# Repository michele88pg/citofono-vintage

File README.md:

# Pronto â€” a smart door intercom inside a vintage rotary phone

ðŸ‡¬ðŸ‡§ English Â· [ðŸ‡®ðŸ‡¹ Italiano](#-versione-italiana)

**Pronto** is an open-hardware circuit board that turns a vintage rotary phone into a **smart door intercom**. The phone looks and works exactly as before:

- lift the handset to talk to whoever rang;
- dial a number and the street door opens.

On top of that you get:

- a notification on your phone when someone rings;
- remote door opening;
- Home Assistant integration and, through Home Assistant, Google Home, Apple Home and Alexa.

The board has **exactly the shape of the original one** and screws into its place, with no drilling or changes to the shell.

> **Compatibility:** **Siemens / Italtel S62** phones (wall-mounted version) and **URMET 4+N** analog intercom systems, very common in Italian apartment buildings.
> Other phones and systems: see [Compatibility](docs/compatibilita.md) (in Italian).

---

> [!WARNING]
> **Prototype stage.** Board rev 0.5 has been ordered (5 assembled boards) but **has not been tested yet**.
> The firmware is validated, but not yet tried on real hardware.
> You are welcome to build one now, but expect to fix something along the way. Current status is in the [CHANGELOG](CHANGELOG.md).

## Contents

- [What it does](#what-it-does)
- [How it works, in short](#how-it-works-in-short)
- [Board pinout](#board-pinout)
- [What you need](#what-you-need)
- [Getting started](#getting-started)
- [Repository layout](#repository-layout)
- [Roadmap](#roadmap)
- [Safety](#safety)
- [Contributing](#contributing)
- [Licenses](#licenses)
- [ðŸ‡®ðŸ‡¹ Versione italiana](#-versione-italiana)

## What it does

| Feature | How it works |
|---|---|
| **Answering** | As always: lift the handset and talk. Audio passes through in analog form; the board does not touch it |
| **Open with the dial** | Dial any number and the door opens, as many vintage intercom phones did. Optional: a **secret code** to dial |
| **Ringing** | When someone rings at the street door, the board's buzzer plays a classic double ring. The phone's original bells can be connected experimentally |
| **Phone notification** | A notification arrives with an **"Open the door"** button in it |
| **Remote opening** | From Home Assistant, the notification, a voice assistant or the board's own web page |
| **Do not disturb** | Silences the ring; the notification still arrives |
| **Auto-open** | Opens by itself when someone rings, handy for parties or expected deliveries. Turns itself off on reboot |
| **History** | Last call, last opening, call counter |
| **Local web page** | `http://citofono-vintage.local` works even without Home Assistant |
| **Remote listening and talking** | *In development:* an add-on audio board with an ES8311 codec. See [hardware/audio-board](hardware/audio-board/README.md) |

## How it works, in short

```mermaid
flowchart LR
    subgraph IMP["URMET 4+N intercom system"]
        CA["CA: call"]
        APR["9 and 6: door release"]
        FON["1 and 2: audio"]
    end
    subgraph SCH["Pronto board, inside the phone"]
        OK1["OK1 optocoupler<br/>detects the call"]
        K1["K1 PhotoMOS<br/>opens the door"]
        K2["K2 PhotoMOS<br/>simulates handset lifted"]
        ESP["ESP32-S3<br/>ESPHome firmware"]
        BZ["Buzzer"]
    end
    subgraph TEL["Rotary phone"]
        DISCO["Rotary dial"]
        CORN["Handset and hook switch"]
    end
    HA["Home Assistant<br/>notifications, Google, Apple, Alexa"]
    CA --> OK1 --> ESP
    ESP --> K1 --> APR
    ESP --> K2 -->|enables| FON
    DISCO --> ESP
    CORN --> ESP
    FON <-->|analog audio| CORN
    ESP --> BZ
    ESP <-->|WiFi| HA
```

**Isolation from the building system.** The board has no direct electrical connection to the shared intercom line. It detects the call with an optocoupler and opens the door with PhotoMOS solid-state relays, which are optically isolated. The electronics' ground stays separate from the intercom line.

The full description is in **[docs/come-funziona.md](docs/come-funziona.md)** (in Italian): every circuit block, the opening sequences, dial timing and firmware safety features.

## Board pinout

The labels are in Italian. Key terms:

| Label | Meaning |
|---|---|
| alimentazione | power input |
| cornetta, capsula, microfono | handset, earpiece, microphone |
| gancio | hook switch |
| fonia entrata / uscita | audio in (from street) / audio out (to street) |
| comune | common |
| apriporta | door release |
| chiamata | call |
| suoneria | ringer bells |
| disco, impulsi, rotazione | dial, pulses, dial-in-motion contact |
| massa | ground |
| zona linea / zona logica | intercom-line side / isolated logic side |
| barriera di isolamento | isolation barrier |

Step-by-step wiring of dial, hook, handset and intercom is in [docs/installazione.md](docs/installazione.md).

## What you need

| Item | Notes |
|---|---|
| An **S62 wall phone** | Found at flea markets and online. Dial, handset and hook switch must work |
| The **Pronto** board | Order it pre-assembled from JLCPCB with the ready-made files in [`hardware/mainboard/production`](hardware/mainboard/production): see [Ordering the board](docs/ordinare-la-scheda.md) |
| Hand-soldered parts | The K1 relay (through-hole, from DigiKey/Mouser) and the screw terminals. Easy soldering |
| **Power** | URMET 4+N systems do not power the indoor unit. You need a supply on J1, **9â€“36 V DC or 9â€“24 V AC** (for example 12 V DC, 1 A), or **5 V from USB-C** |
| Home WiFi | Home Assistant is recommended but not required |
| Tools | Soldering iron, multimeter, screwdriver. A computer with [ESPHome](https://esphome.io) for the first firmware upload over USB-C |

Indicative parts cost is about â‚¬40 per board for 5 assembled prototypes. It drops a lot with larger quantities.

## Getting started

The detailed guides are currently in Italian; translations are welcome.

1. **Check compatibility** of your intercom and phone: [docs/compatibilita.md](docs/compatibilita.md)
2. **Order and assemble the board:** [docs/ordinare-la-scheda.md](docs/ordinare-la-scheda.md)
3. **Upload the firmware:** [firmware/README.md](firmware/README.md)
4. **Install the board in the phone and wire it to the intercom:** [docs/installazione.md](docs/installazione.md)
5. **Test it, one step at a time:** [docs/collaudo.md](docs/collaudo.md)
6. **Connect Home Assistant and notifications:** [docs/home-assistant.md](docs/home-assistant.md)

FAQ: [docs/faq.md](docs/faq.md)

## Repository layout

```
citofono-vintage/
â”œâ”€â”€ hardware/
â”‚   â”œâ”€â”€ mainboard/          Main board (KiCad): schematic, PCB, PDF
â”‚   â”‚   â””â”€â”€ production/     Gerber, BOM and placement files ready for JLCPCB
â”‚   â”œâ”€â”€ audio-board/        ES8311 audio board (remote listen/talk), schematic only
â”‚   â””â”€â”€ mechanical/         S62 board outline as DXF
â”œâ”€â”€ firmware/               ESPHome firmware (+ package for the audio board)
â”œâ”€â”€ home-assistant/         Example automations (notification with "Open" button)
â”œâ”€â”€ docs/                   Documentation: how it works, installation, testing...
â”œâ”€â”€ LICENSES/               License texts
â””â”€â”€ CHANGELOG.md            Revision history
```

## Roadmap

- [x] Mechanical survey of the original S62 board and DXF outline
- [x] Schematic and PCB rev 0.5 in the original board's shape
- [x] ESPHome firmware with dial opening, notifications and remote opening
- [x] Audio board schematic (ES8311) for remote listening and talking
- [ ] Testing the rev 0.5 prototypes on a real URMET system
- [ ] Audio board PCB and voice calls on the phone
- [ ] Photo assembly guide and project website
- [ ] Cheaper, simplified board (ESP32 chip directly on the board, fewer parts)
- [ ] Support for other 4+N systems and other rotary phones
- [ ] English translation of the documentation

## Safety

- The board works only with **extra-low voltages**: 12 V AC call signal, at most about 30 V DC on the intercom line, 9â€“36 V supply. **Never connect it to 230 V mains.**
- The intercom system is often **shared by the whole building**. Make sure you are allowed to work on your indoor unit. Disconnect the old intercom only after identifying the terminals with a multimeter.
- Remote opening really opens your front door. Protect Home Assistant and the board's web page with strong passwords, and never expose the board directly to the Internet.
- The project is provided **as is**, without warranty (see [Licenses](#licenses)). Whoever builds and installs it is responsible for it.

## Contributing

The most valuable contribution right now is knowing **which intercom systems and phones it works with**.
If you try it, open a [compatibility report](../../issues/new?template=compatibilita.md), even if it does not work. Include make and model of the intercom and phone, and your measurements.

Fixes, assembly photos and translations are welcome: see [CONTRIBUTING.md](CONTRIBUTING.md).

## Licenses

| Part | License |
|---|---|
| Hardware (`hardware/`) | [CERN-OHL-S v2](LICENSES/CERN-OHL-S-2.0.txt) |
| Firmware and configuration (`firmware/`, `home-assistant/`) | [MIT](LICENSES/MIT.txt) |
| Documentation and images (`docs/`, `.md` files) | [CC BY-SA 4.0](LICENSES/CC-BY-SA-4.0.txt) |

Details are in [LICENSE.md](LICENSE.md).

**Trademarks.** Siemens, Italtel and URMET are trademarks of their respective owners. They are mentioned only to indicate compatibility. This is an independent project, not affiliated with or endorsed by them.
The S62 phone is a classic of Italian industrial design, designed by Lino Saltini in the 1960s. This project does not reproduce its shell: it only replaces the electronics inside.

---

## ðŸ‡®ðŸ‡¹ Versione italiana

[ðŸ‡¬ðŸ‡§ English](#contents) Â· ðŸ‡®ðŸ‡¹ Italiano

**Pronto â€” il citofono smart dentro un telefono a disco**

**Pronto** Ã¨ una scheda elettronica open hardware che trasforma un telefono a disco d'epoca in un **citofono smart**. Il telefono resta com'Ã¨, fuori e nell'uso:

- alzi la cornetta per parlare con chi ha suonato;
- componi un numero con il disco e il portone si apre.

In piÃ¹ arrivano:

- la notifica sul cellulare quando qualcuno suona;
- l'apertura del portone da remoto;
- l'integrazione con Home Assistant e, tramite Home Assistant, con Google Home, Apple Home e Alexa.

La scheda ha **esattamente la forma della scheda originale** e si avvita al suo posto, senza forare nÃ© modificare il guscio.

> **CompatibilitÃ :** telefoni **Siemens / Italtel S62** (versione da parete) e impianti citofonici **URMET 4+N** analogici.
> Altri telefoni e impianti: vedi [CompatibilitÃ ](docs/compatibilita.md).

> [!WARNING]
> **Progetto in fase di prototipo.** La scheda rev 0.5 Ã¨ stata ordinata (5 esemplari assemblati) ma **non Ã¨ ancora stata collaudata**.
> Il firmware Ã¨ validato, ma non ancora provato sull'hardware vero.
> Se vuoi costruirla adesso sei il benvenuto, ma aspettati di dover correggere qualcosa. Lo stato aggiornato Ã¨ nel [CHANGELOG](CHANGELOG.md).

### Indice

- [Cosa fa](#cosa-fa)
- [Come funziona in breve](#come-funziona-in-breve)
- [Mappa dei morsetti](#mappa-dei-morsetti)
- [Cosa serve](#cosa-serve)
- [Da dove iniziare](#da-dove-iniziare)
- [Struttura della repository](#struttura-della-repository)
- [Prossimi passi](#prossimi-passi)
- [Sicurezza](#sicurezza)
- [Contribuire](#contribuire)
- [Licenze](#licenze)

### Cosa fa

| Funzione | Come si usa |
|---|---|
| **Rispondere** | Come sempre: alzi la cornetta e parli. L'audio passa in analogico, la scheda non lo tocca |
| **Aprire con il disco** | Componi un numero qualsiasi e il portone si apre, come facevano molti citofoni-telefono d'epoca. Opzionale: un **codice segreto** da comporre |
| **Suoneria** | Quando suonano al portone, il buzzer della scheda squilla con un doppio squillo da telefono. La suoneria originale a campanelli si puÃ² collegare in via sperimentale |
| **Notifica sul cellulare** | Arriva una notifica con il pulsante **"Apri il portone"** dentro |
| **Apertura remota** | Da Home Assistant, dalla notifica, dall'assistente vocale o dalla pagina web della scheda |
| **Non disturbare** | Silenzia lo squillo; la notifica arriva comunque |
| **Apertura automatica** | Apre da sola alla chiamata, utile per feste o consegne attese. Si disattiva da sola al riavvio |
| **Storico** | Ultima chiamata, ultima apertura, contatore delle chiamate |
| **Pagina web locale** | `http://citofono-vintage.local` funziona anche senza Home Assistant |
| **Ascolto e risposta da remoto** | *In sviluppo:* scheda audio aggiuntiva con codec ES8311. Vedi [hardware/audio-board](hardware/audio-board/README.md) |

### Come funziona in breve

```mermaid
flowchart LR
    subgraph IMP["Impianto citofonico URMET 4+N"]
        CA["CA: chiamata"]
        APR["9 e 6: apriporta"]
        FON["1 e 2: fonia"]
    end
    subgraph SCH["Scheda Pronto, dentro il telefono"]
        OK1["OK1 optoisolatore<br/>sente la chiamata"]
        K1["K1 PhotoMOS<br/>apre il portone"]
        K2["K2 PhotoMOS<br/>simula la cornetta alzata"]
        ESP["ESP32-S3<br/>firmware ESPHome"]
        BZ["Buzzer"]
    end
    subgraph TEL["Telefono a disco"]
        DISCO["Disco combinatore"]
        CORN["Cornetta e gancio"]
    end
    HA["Home Assistant<br/>notifiche, Google, Apple, Alexa"]
    CA --> OK1 --> ESP
    ESP --> K1 --> APR
    ESP --> K2 -->|abilita| FON
    DISCO --> ESP
    CORN --> ESP
    FON <-->|audio analogico| CORN
    ESP --> BZ
    ESP <-->|WiFi| HA
```

**Isolamento dall'impianto.** La scheda non ha nessun collegamento elettrico diretto con l'impianto condominiale. Sente la chiamata con un optoisolatore e apre il portone con relÃ¨ allo stato solido PhotoMOS, che isolano otticamente. La massa dell'elettronica resta cosÃ¬ separata dalla linea del citofono.

Il funzionamento completo Ã¨ in **[docs/come-funziona.md](docs/come-funziona.md)**: ogni blocco del circuito, le sequenze di apertura, i tempi del disco e le sicurezze del firmware.

### Mappa dei morsetti

Il collegamento passo passo di disco, gancio, cornetta e citofono Ã¨ in [docs/installazione.md](docs/installazione.md).

### Cosa serve

| Cosa | Note |
|---|---|
| Un telefono **S62 da parete** | Si trova nei mercatini e online. Deve avere disco, cornetta e gancio funzionanti |
| La scheda **Pronto** | Si ordina giÃ  assemblata da JLCPCB con i file pronti in [`hardware/mainboard/production`](hardware/mainboard/production): vedi [Ordinare la scheda](docs/ordinare-la-scheda.md) |
| Componenti da saldare a mano | Il relÃ¨ K1 (a foro passante, da DigiKey/Mouser) e le morsettiere a vite. Sono saldature facili |
| **Alimentazione** | L'impianto URMET 4+N non alimenta il posto interno. Serve un alimentatore su J1, **9â€“36 V DC o 9â€“24 V AC** (per esempio 12 V DC da 1 A), oppure **5 V da USB-C** |
| WiFi di casa | Home Assistant Ã¨ consigliato ma non obbligatorio |
| Attrezzatura | Saldatore, tester, cacciavite. Un computer con [ESPHome](https://esphome.io) per il primo caricamento del firmware via USB-C |

Il costo indicativo dei componenti Ã¨ di circa 40 â‚¬ a scheda su 5 prototipi assemblati. Scende molto con quantitÃ  maggiori.

### Da dove iniziare

1. **Verifica la compatibilitÃ ** del tuo impianto e del tuo telefono: [docs/compatibilita.md](docs/compatibilita.md)
2. **Ordina e monta la scheda:** [docs/ordinare-la-scheda.md](docs/ordinare-la-scheda.md)
3. **Carica il firmware:** [firmware/README.md](firmware/README.md)
4. **Installa la scheda nel telefono e collegala al citofono:** [docs/installazione.md](docs/installazione.md)
5. **Collauda, un passo alla volta:** [docs/collaudo.md](docs/collaudo.md)
6. **Collega Home Assistant e le notifiche:** [docs/home-assistant.md](docs/home-assistant.md)

Domande frequenti: [docs/faq.md](docs/faq.md)

### Struttura della repository

```
citofono-vintage/
â”œâ”€â”€ hardware/
â”‚   â”œâ”€â”€ mainboard/          Scheda principale (KiCad): schema, PCB, PDF
â”‚   â”‚   â””â”€â”€ production/     Gerber, BOM e posizionamento pronti per JLCPCB
â”‚   â”œâ”€â”€ audio-board/        Scheda audio ES8311 (ascolto e risposta da remoto), solo schema
â”‚   â””â”€â”€ mechanical/         Contorno della scheda S62 in DXF
â”œâ”€â”€ firmware/               Firmware ESPHome (+ pacchetto per la scheda audio)
â”œâ”€â”€ home-assistant/         Automazioni di esempio (notifica con pulsante "Apri")
â”œâ”€â”€ docs/                   Documentazione: funzionamento, installazione, collaudo...
â”œâ”€â”€ LICENSES/               Testi delle licenze
â””â”€â”€ CHANGELOG.md            Storia delle revisioni
```

### Prossimi passi

- [x] Rilievo meccanico della scheda originale S62 e contorno in DXF
- [x] Schema elettrico e PCB rev 0.5 nella forma della scheda originale
- [x] Firmware ESPHome con apertura da disco, notifiche e apertura remota
- [x] Schema della scheda audio (ES8311) per ascolto e risposta da remoto
- [ ] Collaudo dei prototipi rev 0.5 su impianto URMET reale
- [ ] PCB della scheda audio e integrazione della chiamata vocale sul cellulare
- [ ] Guida fotografica al montaggio e sito del progetto
- [ ] Versione piÃ¹ economica e semplificata della scheda (ESP32 direttamente sulla scheda, meno componenti)
- [ ] CompatibilitÃ  con altri impianti 4+N e con altri telefoni a disco
- [ ] Traduzione in inglese della documentazione

### Sicurezza

- La scheda lavora solo con **bassissime tensioni**: 12 V AC di chiamata, al massimo circa 30 V DC sulla linea citofonica, 9â€“36 V di alimentazione. **Non va mai collegata alla rete a 230 V.**
- L'impianto citofonico Ã¨ spesso **condominiale**. Prima di intervenire sul tuo posto interno, verifica di poterlo fare. Scollega il vecchio citofono solo dopo aver identificato i morsetti con il tester.
- L'apertura remota apre davvero il portone di casa. Proteggi Home Assistant e la pagina web della scheda con password robuste, e non esporre la scheda direttamente su Internet.
- Il progetto Ã¨ fornito **cosÃ¬ com'Ã¨**, senza garanzie (vedi [Licenze](#licenze)). Chi lo costruisce e lo installa ne Ã¨ responsabile.

### Contribuire

Il contributo piÃ¹ prezioso adesso Ã¨ sapere **su quali impianti e telefoni funziona**.
Se lo provi, apri una [segnalazione di compatibilitÃ ](../../issues/new?template=compatibilita.md), anche se non funziona. Servono marca e modello dell'impianto e del telefono, e le misure fatte.

Correzioni, foto del montaggio e traduzioni sono benvenute: vedi [CONTRIBUTING.md](CONTRIBUTING.md).

### Licenze

| Parte | Licenza |
|---|---|
| Hardware (`hardware/`) | [CERN-OHL-S v2](LICENSES/CERN-OHL-S-2.0.txt) |
| Firmware e configurazioni (`firmware/`, `home-assistant/`) | [MIT](LICENSES/MIT.txt) |
| Documentazione e immagini (`docs/`, file `.md`) | [CC BY-SA 4.0](LICENSES/CC-BY-SA-4.0.txt) |

I dettagli sono in [LICENSE.md](LICENSE.md).

**Marchi.** Siemens, Italtel e URMET sono marchi dei rispettivi proprietari. Sono citati solo per indicare la compatibilitÃ . Questo Ã¨ un progetto indipendente, non affiliato nÃ© approvato da loro.
Il telefono S62 Ã¨ un classico del design industriale italiano, disegnato da Lino Saltini negli anni '60. Questo progetto non ne riproduce il guscio: ne sostituisce solo l'elettronica interna.

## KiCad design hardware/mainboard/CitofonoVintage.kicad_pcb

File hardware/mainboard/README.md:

# Scheda principale (rev 0.5)

## File

| File | Contenuto |
|---|---|
| `CitofonoVintage.kicad_pro` | Progetto KiCad: apri questo. Contiene regole e classi di rete |
| `CitofonoVintage.kicad_sch` | Schema elettrico, con il campo **LCSC Part#** su ogni componente |
| `CitofonoVintage.kicad_pcb` | Circuito stampato sbrogliato |
| `CitofonoVintage_schematic.pdf` | Schema stampabile |
| `board_layers.pdf` | Strati del PCB. Stampato in scala 1:1 serve a verificare l'ingombro nel telefono |
| [`production/`](production) | Gerber, BOM e CPL per l'ordine assemblato su JLCPCB |

Il progetto è stato sviluppato con **KiCad 10**, che apre anche i file dei formati precedenti. Tutti i simboli e i footprint vengono dalle librerie ufficiali di KiCad e sono incorporati nei file, quindi non servono librerie esterne.

## Caratteristiche

| | |
|---|---|
| Dimensioni | 81 × 85 mm, contorno identico alla scheda originale S62 ([DXF](../mechanical/S62_board_outline.dxf)) |
| Strati | 2, FR-4 da 1,6 mm, rame da 1 oz |
| Alimentazione | 9–36 V DC o 9–24 V AC su J1, oppure 5 V da USB-C |
| Microcontrollore | ESP32-S3-WROOM-1-N16R2 (16 MB flash, 2 MB PSRAM) |
| Interfaccia linea | Optoisolatore PC817 (chiamata), PhotoMOS TLP3546A/AQV252G (apriporta), PhotoMOS CPC1017N (sgancio) |
| Isolamento | Barriera di 2,4 mm senza rame fra zona linea e zona logica |

## Regole di progetto

| Classe | Pista | Isolamento | Via | Reti |
|---|---|---|---|---|
| Default | 0,25 mm | 0,15 mm | 0,6 / 0,3 mm | segnali |
| Power | 0,5 mm | 0,15 mm | 0,8 / 0,4 mm | +5V, +3V3, +5V_BUCK, VIN_RAW, GND, U1_SW |

Minimi: pista 0,2 mm, via 0,5/0,2 mm, distanza dal bordo 0,2 mm. Sono tutti entro le capacità standard di JLCPCB.

**Zone:**
- `GND_plane`: sullo strato inferiore, solo nella zona logica. La massa è anche sbrogliata con piste, quindi il piano non è l'unico collegamento.
- `isolamento_1…6`: le strisce della barriera. Sono vietati piste, via e rame; pad e componenti sono ammessi, perché OK1, K1 e K2 stanno a cavallo.
- `antenna_keepout`: nessun rame sotto l'antenna del modulo ESP32.

**Stato DRC:** 0 connessioni mancanti e 0 violazioni elettriche. Restano solo avvisi di serigrafia sovrapposta, cosmetici.

## Componenti principali

| Rif | Componente | LCSC | Note |
|---|---|---|---|
| U1 | LM5164DDA (buck 1 A, fino a 100 V) | C477928 | |
| U2 | AMS1117-3.3 | C6186 | |
| U3 | ESP32-S3-WROOM-1-N16R2 | C2913205 | Richiede l'assemblaggio "Standard" |
| K1 | TLP3546A(F) o AQV252G, DIP-6 a foro passante | — | Da saldare a mano, da DigiKey o Mouser |
| K2 | CPC1017N | C81521 | |
| OK1 | PC817 | C3025068 | |
| D1 | ABS10 (ponte) | C400507 | |
| D2 | SMAJ36A (TVS) | C2760877 | |
| L1 | SRR1260-470M (47 µH) | C1329363 | |
| BZ1 | TMB12A05 (buzzer attivo 5 V) | C96093 | |
| J2 | USB-C HRO TYPE-C-31-M-12 | C165948 | |

La distinta completa è in [`production/BOM_JLCPCB.csv`](production/BOM_JLCPCB.csv). I componenti da saldare a mano sono elencati in [docs/ordinare-la-scheda.md](../../docs/ordinare-la-scheda.md#componenti-da-saldare-a-mano).

## Da sistemare nella prossima revisione

- La serigrafia di J1 dice "9-40 V": il valore corretto è **9–36 V DC / 9–24 V AC**, limitato dal TVS D2.
- Nel cartiglio dello schema: la revisione è ancora "0.3" e il titolo del blocco B dice ancora "N16R8" (il modulo montato è l'N16R2).
- Avvisi di serigrafia sovrapposta da ripulire.
- Da valutare dopo il collaudo: i valori di R14 (sensibilità della chiamata) e di R15/R16 (corrente nei LED dei PhotoMOS).

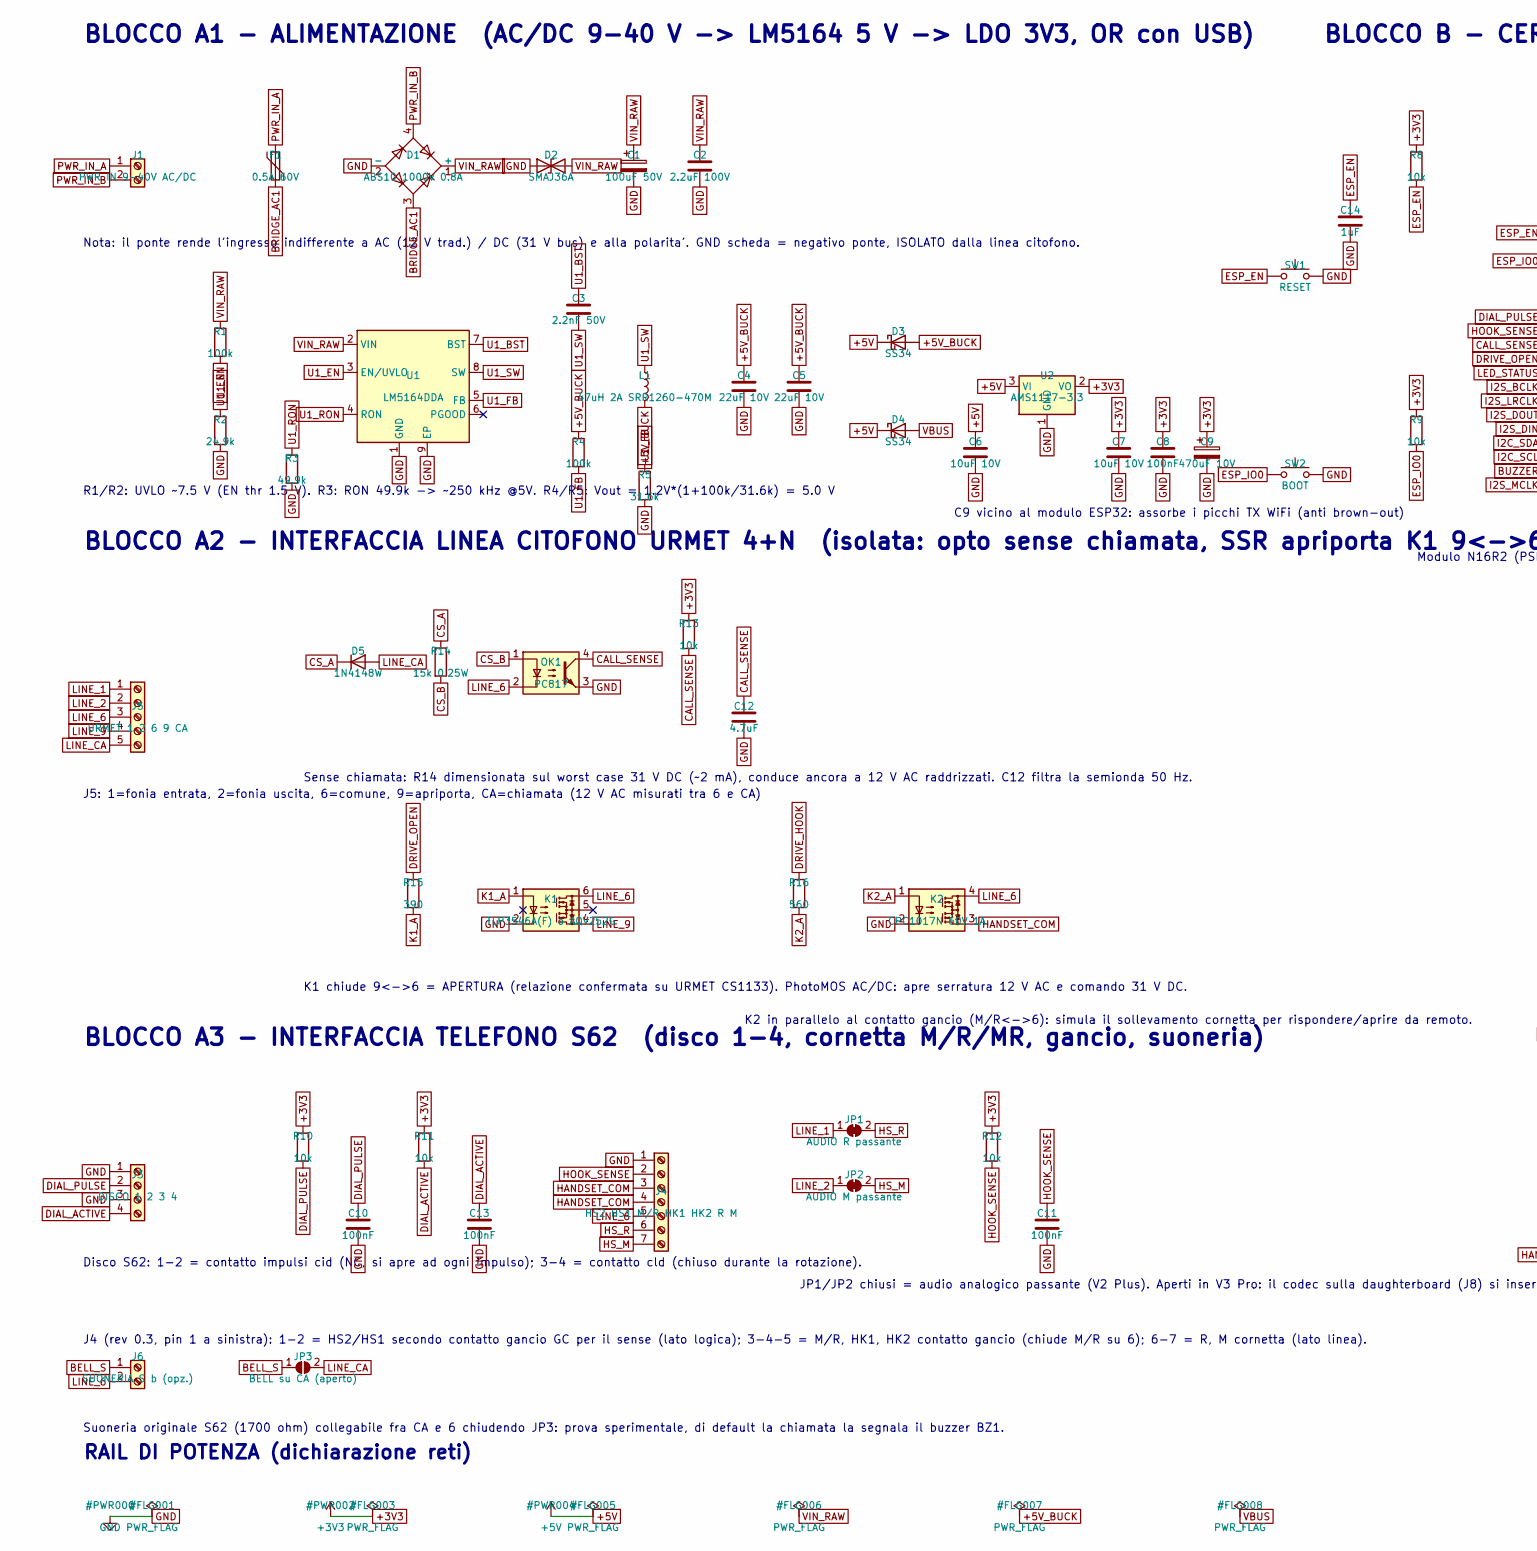
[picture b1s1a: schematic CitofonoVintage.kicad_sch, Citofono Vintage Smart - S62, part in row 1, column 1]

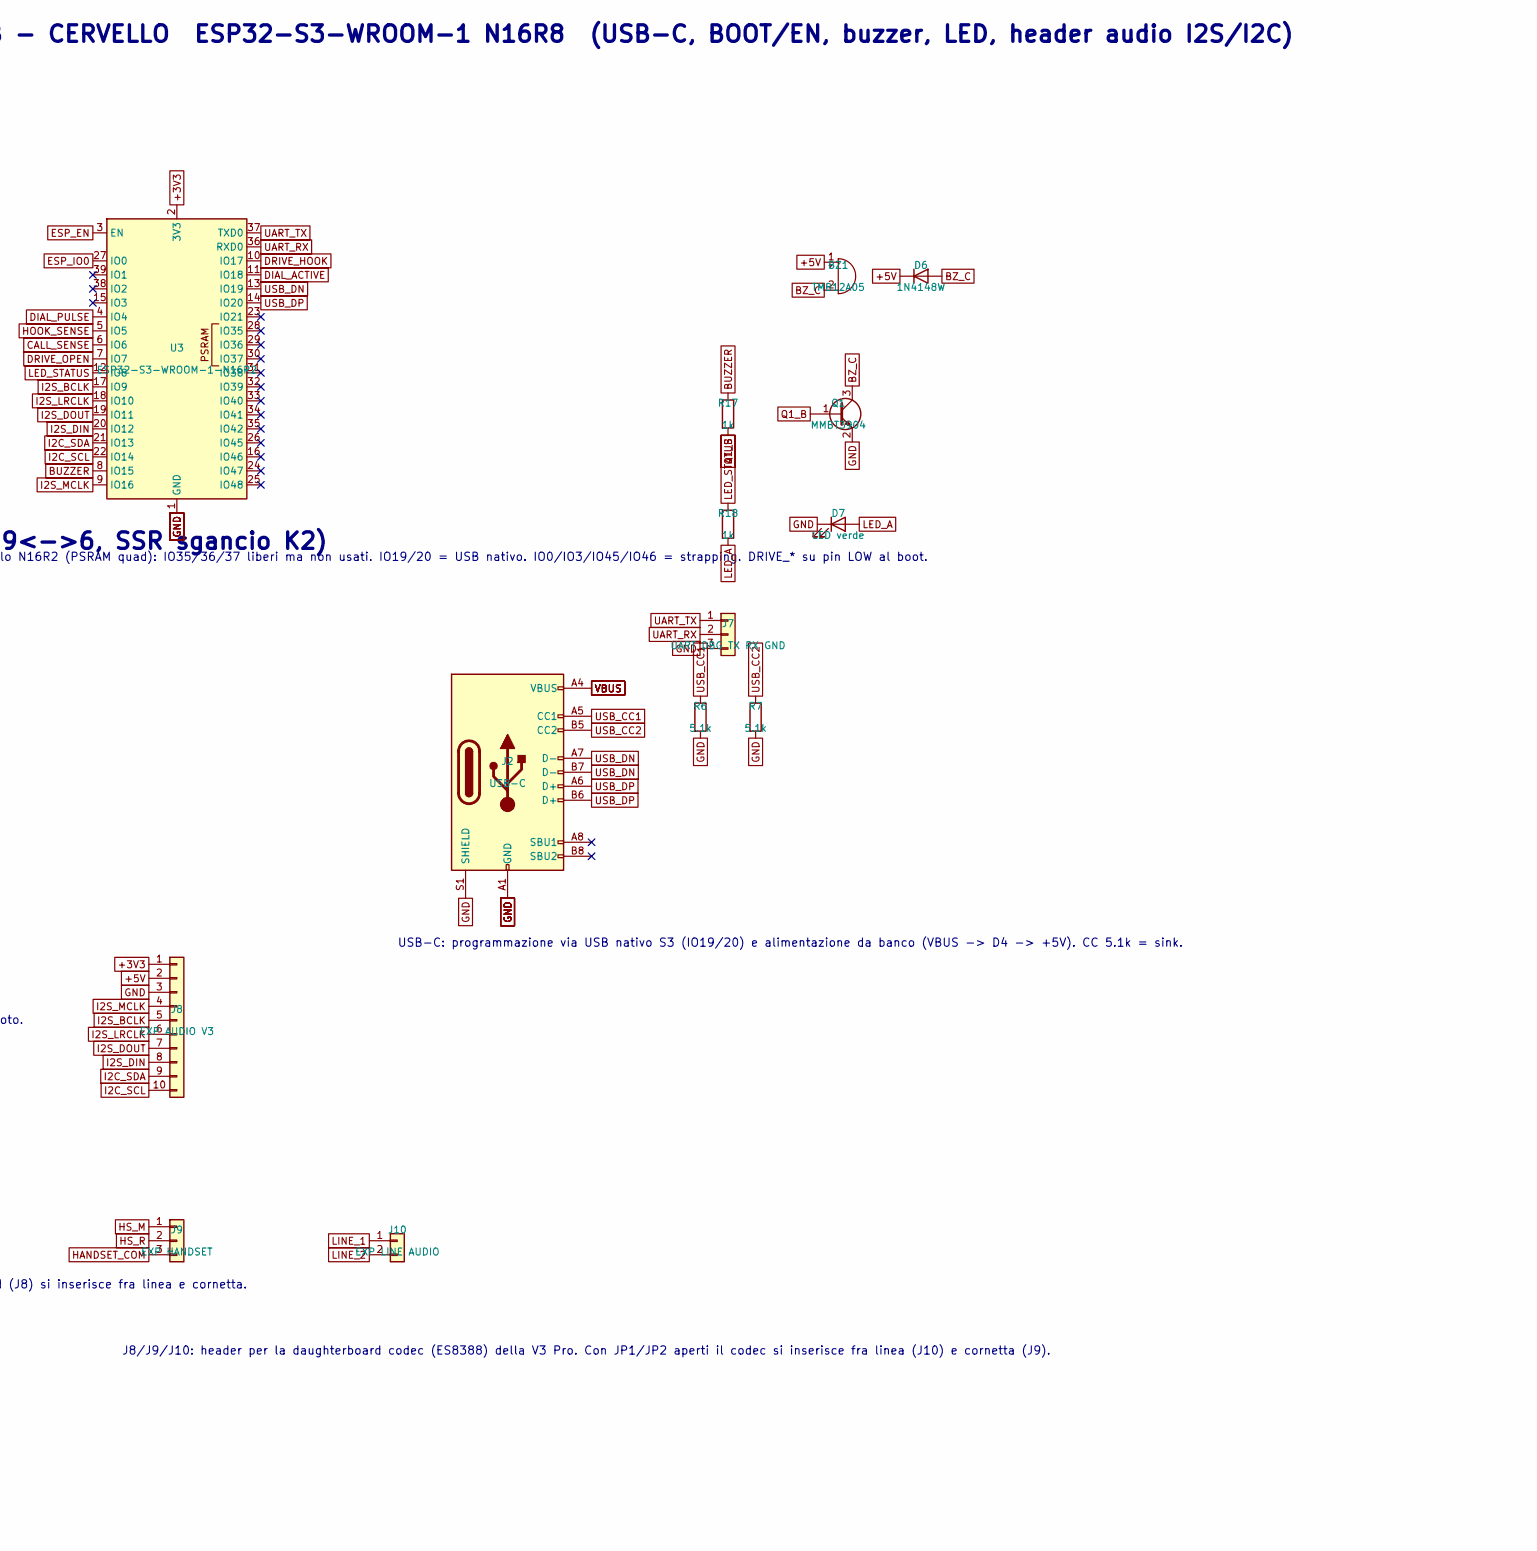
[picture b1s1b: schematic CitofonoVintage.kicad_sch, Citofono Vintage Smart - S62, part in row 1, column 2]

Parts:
BZ1: TMB12A05; Buzzer_12x9.5RM7.6; LCSC Part# C96093
C1: 100uF 50V; CP_Elec_8x10; LCSC Part# C97812
C2: 2.2uF 100V; C_1206_3216Metric; LCSC Part# C577211
C3: 2.2nF 50V; C_0603_1608Metric; LCSC Part# C1604
C4, C5: 22uF 10V; C_0805_2012Metric; LCSC Part# C45783
C6, C7: 10uF 10V; C_0805_2012Metric; LCSC Part# C15850
C8, C10, C11, C13: 100nF; C_0603_1608Metric; LCSC Part# C14663
C9: 470uF 10V; CP_Elec_8x10; LCSC Part# C970706
C12: 4.7uF; C_0805_2012Metric; LCSC Part# C1779
C14: 1uF; C_0603_1608Metric; LCSC Part# C15849
D1: ABS10 1000V 0.8A; Diode_Bridge_Diotec_ABS; LCSC Part# C400507
D2: SMAJ36A; D_SMA; LCSC Part# C2760877
D3, D4: SS34; D_SMA; LCSC Part# C8678
D5, D6: 1N4148W; D_SOD-123; LCSC Part# C81598
D7: LED verde; LED_0805_2012Metric; LCSC Part# C2297
F1: 0.5A 60V; Fuse_1812_4532Metric; LCSC Part# C462518
J1: PWR IN 9-40V AC/DC; TerminalBlock_Phoenix_MKDS-1,5-2_1x02_P5.00mm_Horizontal
J2: USB-C; USB_C_Receptacle_HRO_TYPE-C-31-M-12; LCSC Part# C165948
J3: DISCO 1 2 3 4; TerminalBlock_Phoenix_MKDS-1,5-4_1x04_P5.00mm_Horizontal
J4: HS2 HS1 M/R HK1 HK2 R M; TerminalBlock_Phoenix_MKDS-1,5-7_1x07_P5.00mm_Horizontal
J5: URMET 1 2 6 9 CA; TerminalBlock_Phoenix_MKDS-1,5-5_1x05_P5.00mm_Horizontal
J6: SUONERIA S b (opz.); TerminalBlock_Phoenix_MKDS-1,5-2_1x02_P5.00mm_Horizontal
J7: UART DBG TX RX GND; PinHeader_1x03_P2.54mm_Vertical
J8: EXP AUDIO V3; PinHeader_1x10_P2.54mm_Vertical
J9: EXP HANDSET; PinHeader_1x03_P2.54mm_Vertical
J10: EXP LINE AUDIO; PinHeader_1x02_P2.54mm_Vertical
JP1: AUDIO R passante; SolderJumper-2_P1.3mm_Bridged_RoundedPad1.0x1.5mm
JP2: AUDIO M passante; SolderJumper-2_P1.3mm_Bridged_RoundedPad1.0x1.5mm
JP3: BELL su CA (aperto); SolderJumper-2_P1.3mm_Open_RoundedPad1.0x1.5mm
K1: TLP3546A(F) o AQV252G; DIP-6_W7.62mm
K2: CPC1017N 60V 1A; SOP-4_3.8x4.1mm_P2.54mm; LCSC Part# C81521
L1: 47uH 2A SRR1260-470M; L_Bourns_SRR1260; LCSC Part# C1329363
OK1: PC817; DIP-4_W7.62mm; LCSC Part# C3025068
Q1: MMBT3904; SOT-23; LCSC Part# C20526
R1, R4: 100k; R_0603_1608Metric; LCSC Part# C25803
R2: 24.9k; R_0603_1608Metric; LCSC Part# C25962
R3: 49.9k; R_0603_1608Metric; LCSC Part# C23184
R5: 31.6k; R_0603_1608Metric; LCSC Part# C25967
R6, R7: 5.1k; R_0603_1608Metric; LCSC Part# C23186
R8, R9, R10, R11, R12, R13: 10k; R_0603_1608Metric; LCSC Part# C25804
R14: 15k 0.25W; R_1206_3216Metric; LCSC Part# C114932
R15: 390; R_0603_1608Metric; LCSC Part# C23151
R16: 560; R_0603_1608Metric; LCSC Part# C23204
R17, R18: 1k; R_0603_1608Metric; LCSC Part# C21190
SW1: RESET; SW_SPST_TL3305A; LCSC Part# C2886899
SW2: BOOT; SW_SPST_TL3305A; LCSC Part# C2886899
U1: LM5164DDA; Texas_HSOP-8-1EP_3.9x4.9mm_P1.27mm; LCSC Part# C477928
U2: AMS1117-3.3; SOT-223-3_TabPin2; LCSC Part# C6186
U3: ESP32-S3-WROOM-1-N16R2; ESP32-S3-WROOM-1; LCSC Part# C2913205

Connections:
+3V3: C7.1, C8.1, C9.1, J8.1, R8.1, R9.1, R10.1, R11.1, R12.1, R13.1, U2.2 (VO), U3.2 (3V3)
+5V: BZ1.1 (+), C6.1, D3.1 (K), D4.1 (K), D6.1 (K), J8.2, U2.3 (VI)
+5V_BUCK: C4.1, C5.1, D3.2 (A), L1.2, R4.1
BELL_S: J6.1, JP3.1 (A)
BRIDGE_AC1: D1.3, F1.2
BUZZER: R17.1, U3.8 (IO15)
BZ_C: BZ1.2 (-), D6.2 (A), Q1.3 (C)
CALL_SENSE: C12.1, OK1.4, R13.2, U3.6 (IO6)
CS_A: D5.1 (K), R14.1
CS_B: OK1.1, R14.2
DIAL_ACTIVE: C13.1, J3.4, R11.2, U3.11 (IO18)
DIAL_PULSE: C10.1, J3.2, R10.2, U3.4 (IO4)
DRIVE_HOOK: R16.1, U3.10 (IO17)
DRIVE_OPEN: R15.1, U3.7 (IO7)
ESP_EN: C14.1, R8.2, SW1.1, U3.3 (EN)
ESP_IO0: R9.2, SW2.1, U3.27 (IO0)
GND: C1.2, C2.2, C4.2, C5.2, C6.2, C7.2, C8.2, C9.2, C10.2, C11.2, C12.2, C13.2, C14.2, D1.2 (-), D2.1 (A1), D7.1 (K), J2.A1 (GND), J2.A12 (GND), J2.B1 (GND), J2.B12 (GND), J2.S1 (SHIELD), J3.1, J3.3, J4.1, J7.3, J8.3, K1.2, K2.2, OK1.3, Q1.2 (E), R2.2, R3.2, R5.2, R6.2, R7.2, SW1.2, SW2.2, U1.1 (GND), U1.9 (EP), U2.1 (GND), U3.1 (GND), U3.40 (GND), U3.41 (GND)
HANDSET_COM: J4.3, J4.4, J9.3, K2.3
HOOK_SENSE: C11.1, J4.2, R12.2, U3.5 (IO5)
HS_M: J4.7, J9.1, JP2.2 (B)
HS_R: J4.6, J9.2, JP1.2 (B)
I2C_SCL: J8.10, U3.22 (IO14)
I2C_SDA: J8.9, U3.21 (IO13)
I2S_BCLK: J8.5, U3.17 (IO9)
I2S_DIN: J8.8, U3.20 (IO12)
I2S_DOUT: J8.7, U3.19 (IO11)
I2S_LRCLK: J8.6, U3.18 (IO10)
I2S_MCLK: J8.4, U3.9 (IO16)
K1_A: K1.1, R15.2
K2_A: K2.1, R16.2
LED_A: D7.2 (A), R18.2
LED_STATUS: R18.1, U3.12 (IO8)
LINE_1: J5.1, J10.1, JP1.1 (A)
LINE_2: J5.2, J10.2, JP2.1 (A)
LINE_6: J4.5, J5.3, J6.2, K1.6, K2.4, OK1.2
LINE_9: J5.4, K1.4
LINE_CA: D5.2 (A), J5.5, JP3.2 (B)
PWR_IN_A: F1.1, J1.1
PWR_IN_B: D1.4, J1.2
Q1_B: Q1.1 (B), R17.2
U1_BST: C3.1, U1.7 (BST)
U1_EN: R1.2, R2.1, U1.3 (EN/UVLO)
U1_FB: R4.2, R5.1, U1.5 (FB)
U1_RON: R3.1, U1.4 (RON)
U1_SW: C3.2, L1.1, U1.8 (SW)
UART_RX: J7.2, U3.36 (RXD0)
UART_TX: J7.1, U3.37 (TXD0)
USB_CC1: J2.A5 (CC1), R6.1
USB_CC2: J2.B5 (CC2), R7.1
USB_DN: J2.A7 (D-), J2.B7 (D-), U3.13 (IO19)
USB_DP: J2.A6 (D+), J2.B6 (D+), U3.14 (IO20)
VBUS: D4.2 (A), J2.A4 (VBUS), J2.A9 (VBUS), J2.B4 (VBUS), J2.B9 (VBUS)
VIN_RAW: C1.1, C2.1, D1.1 (+), D2.2 (A2), R1.1, U1.2 (VIN)

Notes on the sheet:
Disco S62: 1-2 = contatto impulsi cid (NC, si apre ad ogni impulso); 3-4 = contatto cld (chiuso durante la rotazione).
J5: 1=fonia entrata, 2=fonia uscita, 6=comune, 9=apriporta, CA=chiamata (12 V AC misurati tra 6 e CA)
J8/J9/J10: header per la daughterboard codec (ES8388) della V3 Pro. Con JP1/JP2 aperti il codec si inserisce fra linea (J10) e cornetta (J9).
JP1/JP2 chiusi = audio analogico passante (V2 Plus). Aperti in V3 Pro: il codec sulla daughterboard (J8) si inserisce fra linea e cornetta.
USB-C: programmazione via USB nativo S3 (IO19/20) e alimentazione da banco (VBUS -> D4 -> +5V). CC 5.1k = sink.
Sense chiamata: R14 dimensionata sul worst case 31 V DC (~2 mA), conduce ancora a 12 V AC raddrizzati. C12 filtra la semionda 50 Hz.
R1/R2: UVLO ~7.5 V (EN thr 1.5 V). R3: RON 49.9k -> ~250 kHz @5V. R4/R5: Vout = 1.2V*(1+100k/31.6k) = 5.0 V
J4 (rev 0.3, pin 1 a sinistra): 1-2 = HS2/HS1 secondo contatto gancio GC per il sense (lato logica); 3-4-5 = M/R, HK1, HK2 contatto gancio (chiude M/R su 6); 6-7 = R, M cornetta (lato linea).
K2 in parallelo al contatto gancio (M/R<->6): simula il sollevamento cornetta per rispondere/aprire da remoto.
BLOCCO A2 - INTERFACCIA LINEA CITOFONO URMET 4+N (isolata: opto sense chiamata, SSR apriporta K1 9<->6, SSR sgancio K2)
Suoneria originale S62 (1700 ohm) collegabile fra CA e 6 chiudendo JP3: prova sperimentale, di default la chiamata la segnala il buzzer BZ1.
Nota: il ponte rende l'ingresso indifferente a AC (12 V trad.) / DC (31 V bus) e alla polarita'. GND scheda = negativo ponte, ISOLATO dalla linea citofono.
C9 vicino al modulo ESP32: assorbe i picchi TX WiFi (anti brown-out)
RAIL DI POTENZA (dichiarazione reti)
K1 chiude 9<->6 = APERTURA (relazione confermata su URMET CS1133). PhotoMOS AC/DC: apre serratura 12 V AC e comando 31 V DC.
BLOCCO B - CERVELLO ESP32-S3-WROOM-1 N16R8 (USB-C, BOOT/EN, buzzer, LED, header audio I2S/I2C)
BLOCCO A1 - ALIMENTAZIONE (AC/DC 9-40 V -> LM5164 5 V -> LDO 3V3, OR con USB)
Modulo N16R2 (PSRAM quad): IO35/36/37 liberi ma non usati. IO19/20 = USB nativo. IO0/IO3/IO45/IO46 = strapping. DRIVE_* su pin LOW al boot.
BLOCCO A3 - INTERFACCIA TELEFONO S62 (disco 1-4, cornetta M/R/MR, gancio, suoneria)

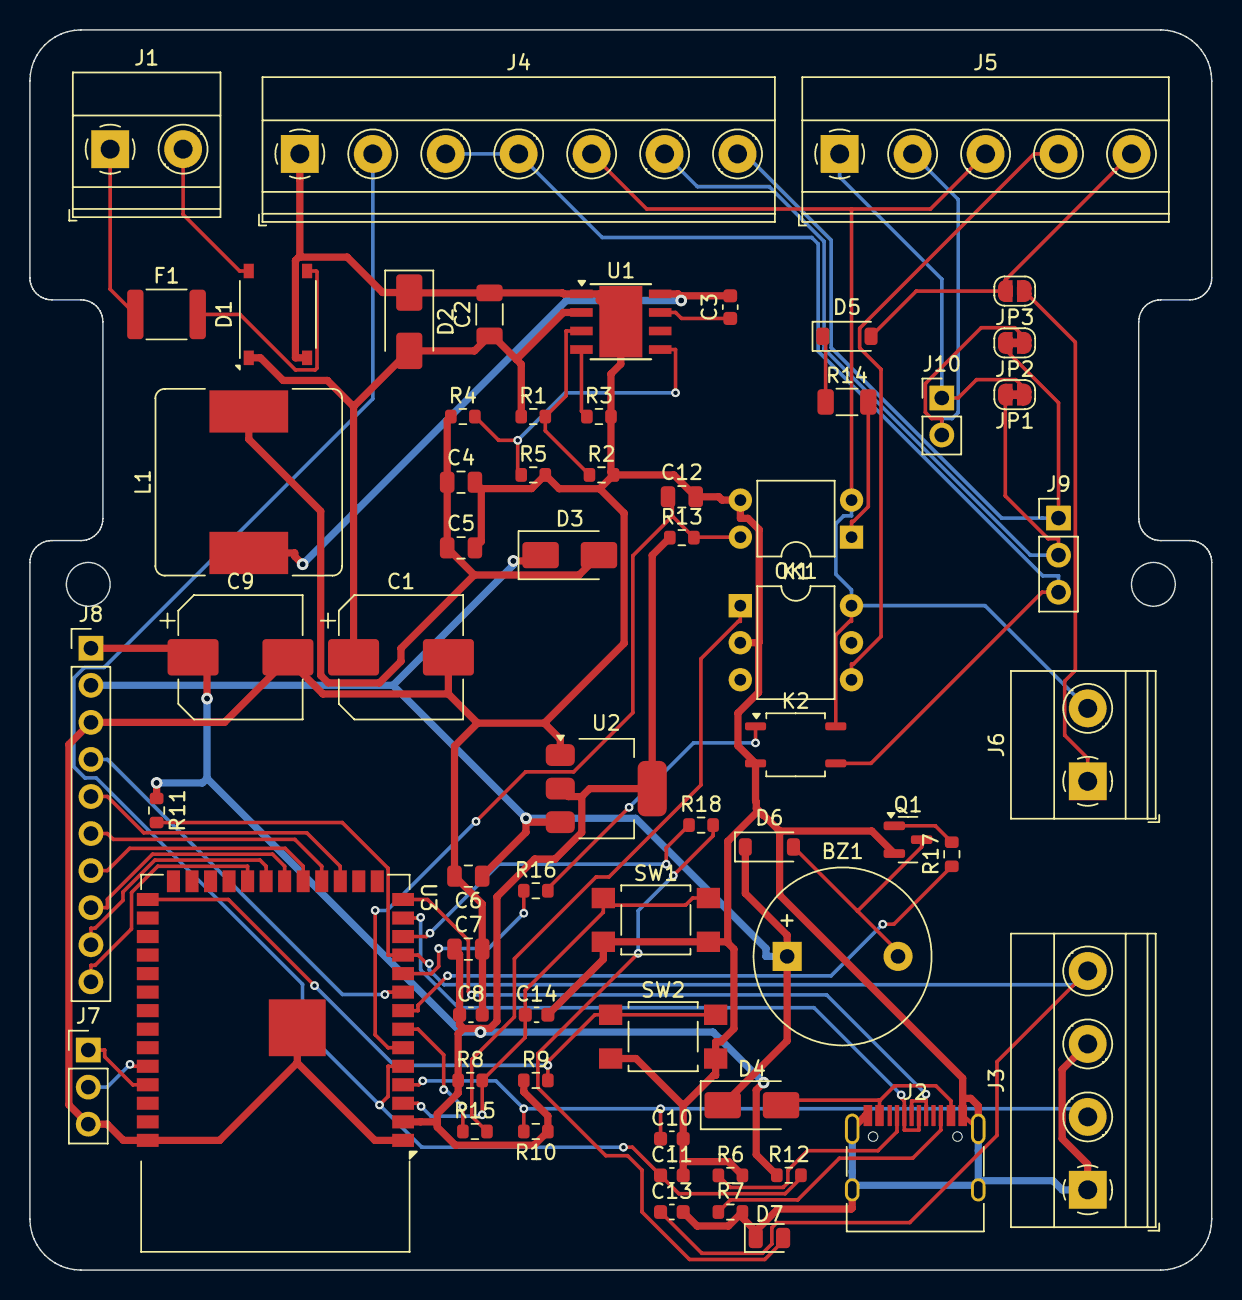
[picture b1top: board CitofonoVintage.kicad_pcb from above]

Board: 2 copper layers, 81.0 x 85.0 mm, 64 parts (0 on the bottom side), 53 nets.

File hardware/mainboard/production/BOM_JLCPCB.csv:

"Reference","Qty","Value","LCSC Part#","DNP","Exclude from BOM","Exclude from Board","Footprint"
"BZ1","1","TMB12A05","C96093","","","","Buzzer_Beeper:Buzzer_12x9.5RM7.6"
"C1","1","100uF 50V","C97812","","","","Capacitor_SMD:CP_Elec_8x10"
"C2","1","2.2uF 100V","C577211","","","","Capacitor_SMD:C_1206_3216Metric"
"C3","1","2.2nF 50V","C1604","","","","Capacitor_SMD:C_0603_1608Metric"
"C4,C5","2","22uF 10V","C45783","","","","Capacitor_SMD:C_0805_2012Metric"
"C6,C7","2","10uF 10V","C15850","","","","Capacitor_SMD:C_0805_2012Metric"
"C8,C10,C11,C13","4","100nF","C14663","","","","Capacitor_SMD:C_0603_1608Metric"
"C9","1","470uF 10V","C970706","","","","Capacitor_SMD:CP_Elec_8x10"
"C12","1","4.7uF","C1779","","","","Capacitor_SMD:C_0805_2012Metric"
"C14","1","1uF","C15849","","","","Capacitor_SMD:C_0603_1608Metric"
"D1","1","ABS10 1000V 0.8A","C400507","","","","Diode_SMD:Diode_Bridge_Diotec_ABS"
"D2","1","SMAJ36A","C2760877","","","","Diode_SMD:D_SMA"
"D3,D4","2","SS34","C8678","","","","Diode_SMD:D_SMA"
"D5,D6","2","1N4148W","C81598","","","","Diode_SMD:D_SOD-123"
"D7","1","LED verde","C2297","","","","LED_SMD:LED_0805_2012Metric"
"F1","1","0.5A 60V","C462518","","","","Fuse:Fuse_1812_4532Metric"
"J2","1","USB-C","C165948","","","","Connector_USB:USB_C_Receptacle_HRO_TYPE-C-31-M-12"
"J3","1","DISCO 1 2 3 4","","","","","TerminalBlock_Phoenix:TerminalBlock_Phoenix_MKDS-1,5-4_1x04_P5.00mm_Horizontal"
"K1","1","TLP3546A(F) o AQV252G","","","","","Package_DIP:DIP-6_W7.62mm"
"K2","1","CPC1017N 60V 1A","C81521","","","","Package_SO:SOP-4_3.8x4.1mm_P2.54mm"
"L1","1","47uH 2A SRR1260-470M","C1329363","","","","Inductor_SMD:L_Bourns_SRR1260"
"OK1","1","PC817","C3025068","","","","Package_DIP:DIP-4_W7.62mm"
"Q1","1","MMBT3904","C20526","","","","Package_TO_SOT_SMD:SOT-23"
"R1,R4","2","100k","C25803","","","","Resistor_SMD:R_0603_1608Metric"
"R2","1","24.9k","C25962","","","","Resistor_SMD:R_0603_1608Metric"
"R3","1","49.9k","C23184","","","","Resistor_SMD:R_0603_1608Metric"
"R5","1","31.6k","C25967","","","","Resistor_SMD:R_0603_1608Metric"
"R6,R7","2","5.1k","C23186","","","","Resistor_SMD:R_0603_1608Metric"
"R8,R9,R10,R11,R12,R13","6","10k","C25804","","","","Resistor_SMD:R_0603_1608Metric"
"R14","1","15k 0.25W","C114932","","","","Resistor_SMD:R_1206_3216Metric"
"R15","1","390","C23151","","","","Resistor_SMD:R_0603_1608Metric"
"R16","1","560","C23204","","","","Resistor_SMD:R_0603_1608Metric"
"R17,R18","2","1k","C21190","","","","Resistor_SMD:R_0603_1608Metric"
"SW1","1","RESET","C2886899","","","","Button_Switch_SMD:SW_SPST_TL3305A"
"SW2","1","BOOT","C2886899","","","","Button_Switch_SMD:SW_SPST_TL3305A"
"U1","1","LM5164DDA","C477928","","","","Package_SO:Texas_HSOP-8-1EP_3.9x4.9mm_P1.27mm"
"U2","1","AMS1117-3.3","C6186","","","","Package_TO_SOT_SMD:SOT-223-3_TabPin2"
"U3","1","ESP32-S3-WROOM-1-N16R2","C2913205","","","","RF_Module:ESP32-S3-WROOM-1"

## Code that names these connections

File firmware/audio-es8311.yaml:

# =============================================================================
#  Pacchetto ESPHome per la SCHEDA AUDIO ES8311 (daughterboard su J8/J9/J10)
#
#  Si aggiunge al firmware principale, in citofono-vintage.yaml:
#
#    packages:
#      audio: !include audio-es8311.yaml
#
#  Mappa (J8 della scheda madre):
#    IO16 MCLK   IO9 BCLK   IO10 LRCLK   IO11 DOUT (ESP -> codec)   IO12 DIN (codec -> ESP)
#    IO13 SDA    IO14 SCL   -> ES8311 @0x18, TCA9554 @0x20
#  TCA9554: P0 = relè audio K1 (linea al codec), P1 = LED "audio remoto" (acceso basso)
#
#  Questo pacchetto rende disponibili microfono (= voce dal posto esterno) e
#  altoparlante (= voce verso il posto esterno). Il componente che li collega
#  al telefono (SIP/WebRTC, es. esphome-intercom) si aggiunge sopra a questi id:
#    microphone: citofono_mic     speaker: citofono_spk     audio_dac: codec
# =============================================================================

i2c:
  id: bus_audio
  sda: GPIO13
  scl: GPIO14
  frequency: 400kHz

i2s_audio:
  - id: i2s_bus
    i2s_lrclk_pin: GPIO10
    i2s_bclk_pin: GPIO9
    i2s_mclk_pin: GPIO16

audio_dac:
  - platform: es8311
    id: codec
    i2c_id: bus_audio
    address: 0x18
    use_mclk: true
    use_microphone: true
    # Il segnale arriva attenuato di ~17 dB dalla presa ad alta impedenza:
    # si parte da 24 dB e si regola al collaudo (0DB ... 42DB)
    mic_gain: 24DB
    sample_rate: 16000
    bits_per_sample: 16bit

microphone:
  - platform: i2s_audio
    id: citofono_mic
    i2s_audio_id: i2s_bus
    i2s_din_pin: GPIO12
    adc_type: external
    pdm: false
    sample_rate: 16000
    bits_per_sample: 16bit
    channel: left

speaker:
  - platform: i2s_audio
    id: citofono_spk
    i2s_audio_id: i2s_bus
    i2s_dout_pin: GPIO11
    dac_type: external
    audio_dac: codec
    sample_rate: 16000
    bits_per_sample: 16bit
    channel: mono

pca9554:
  - id: espansore_audio
    i2c_id: bus_audio
    address: 0x20

switch:
  # Relè K1 della scheda audio: ON = linea collegata al codec (cornetta esclusa)
  - platform: gpio
    id: relay_audio
    name: "Relè audio (scheda ES8311)"
    internal: true
    restore_mode: ALWAYS_OFF
    pin:
      pca9554: espansore_audio
      number: 0
      mode:
        output: true

  - platform: gpio
    id: led_audio
    internal: true
    restore_mode: ALWAYS_OFF
    pin:
      pca9554: espansore_audio
      number: 1
      inverted: true
      mode:
        output: true

  # Comando unico per Home Assistant: "rispondo da remoto"
  - platform: template
    id: remote_audio
    name: "Rispondi da remoto (audio)"
    icon: mdi:phone-in-talk
    optimistic: true
    restore_mode: ALWAYS_OFF
    turn_on_action:
      - switch.turn_on: relay_hook      # K2 scheda madre: impegna la linea URMET
      - delay: 200ms
      - switch.turn_on: relay_audio     # K1 scheda audio: linea -> codec
      - switch.turn_on: led_audio
      - script.execute: remote_audio_timeout
    turn_off_action:
      - script.stop: remote_audio_timeout
      - switch.turn_off: relay_audio
      - switch.turn_off: led_audio
      - switch.turn_off: relay_hook

script:
  # Sicurezza: la conversazione remota si chiude da sola dopo 2 minuti
  - id: remote_audio_timeout
    mode: restart
    then:
      - delay: 120s
      - switch.turn_off: remote_audio

number:
  - platform: template
    id: volume_uscita
    name: "Volume voce verso la strada"
    icon: mdi:volume-high
    min_value: 0
    max_value: 100
    step: 5
    initial_value: 60
    restore_value: true
    optimistic: true
    on_value:
      - lambda: id(codec).set_volume(x / 100.0f);
